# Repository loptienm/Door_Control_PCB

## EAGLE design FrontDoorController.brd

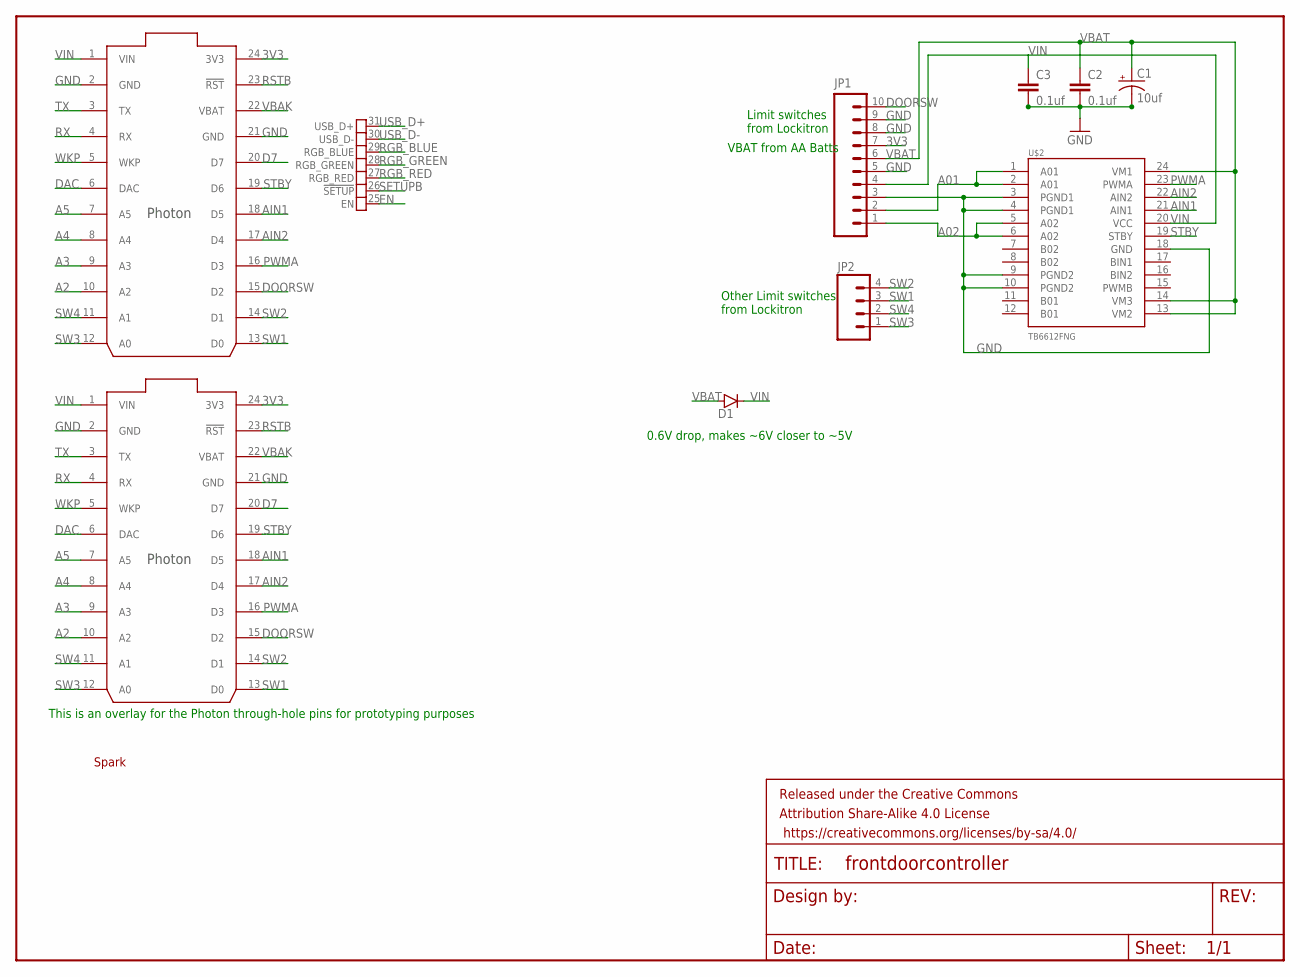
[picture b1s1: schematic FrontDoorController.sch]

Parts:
C1: 10uf; EIA3528
C2, C3: 0.1uf; 0402-CAP
D1: DIODEPTH; DIODE-1N4001
FRAME1: FRAME-LETTER; CREATIVE_COMMONS
JP1: M10LOCK; 1X10_LOCK
JP2: M04LOCK; 1X04_LOCK
PHOTON: PHOTON_SMD
U$1: SPARK_LOGOLARGE; SPARK_LOGO
U$2: TB6612FNG; SSOP24
U$3: PHOTON_WITH_HEADERS; PHOTON

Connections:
3V3: JP1.7, PHOTON.24 (3V3), U$3.24 (3V3)
A01: JP1.2, U$2.1 (A01), U$2.2 (A01)
A2: PHOTON.10 (A2), U$3.10 (A2)
A02: JP1.1, U$2.5 (A02), U$2.6 (A02)
A3: PHOTON.9 (A3), U$3.9 (A3)
A4: PHOTON.8 (A4), U$3.8 (A4)
A5: PHOTON.7 (A5), U$3.7 (A5)
AIN1: PHOTON.18 (D5), U$2.21 (AIN1), U$3.18 (D5)
AIN2: PHOTON.17 (D4), U$2.22 (AIN2), U$3.17 (D4)
D7: PHOTON.20 (D7), U$3.20 (D7)
DAC: PHOTON.6 (DAC), U$3.6 (DAC)
DOORSW: JP1.10, PHOTON.15 (D2), U$3.15 (D2)
EN: PHOTON.25 (EN)
GND: C1.C (-), C2.2, C3.2, JP1.3, JP1.5, JP1.8, JP1.9, PHOTON.2 (GND), PHOTON.21 (GND), U$2.3 (PGND1), U$2.4 (PGND1), U$2.9 (PGND2), U$2.10 (PGND2), U$2.18 (GND), U$3.2 (GND), U$3.21 (GND)
PWMA: PHOTON.16 (D3), U$2.23 (PWMA), U$3.16 (D3)
RGB_BLUE: PHOTON.29 (RGB_BLUE)
RGB_GREEN: PHOTON.28 (RGB_GREEN)
RGB_RED: PHOTON.27 (RGB_RED)
RSTB: PHOTON.23 (!RST), U$3.23 (!RST)
RX: PHOTON.4 (RX), U$3.4 (RX)
SETUPB: PHOTON.26 (!SETUP)
STBY: PHOTON.19 (D6), U$2.19 (STBY), U$3.19 (D6)
SW1: JP2.3, PHOTON.13 (D0), U$3.13 (D0)
SW2: JP2.4, PHOTON.14 (D1), U$3.14 (D1)
SW3: JP2.1, PHOTON.12 (A0), U$3.12 (A0)
SW4: JP2.2, PHOTON.11 (A1), U$3.11 (A1)
TX: PHOTON.3 (TX), U$3.3 (TX)
USB_D+: PHOTON.31 (USB_D+)
USB_D-: PHOTON.30 (USB_D-)
VBAK: PHOTON.22 (VBAT), U$3.22 (VBAT)
VBAT: C1.A (+), C2.1, D1.A, JP1.6, U$2.13 (VM2), U$2.14 (VM3), U$2.24 (VM1)
VIN: C3.1, D1.C, JP1.4, PHOTON.1 (VIN), U$2.20 (VCC), U$3.1 (VIN)
WKP: PHOTON.5 (WKP), U$3.5 (WKP)

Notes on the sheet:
VBAT from AA Batts
0.6V drop, makes ~6V closer to ~5V
This is an overlay for the Photon through-hole pins for prototyping purposes
Limit switches from Lockitron
Other Limit switches from Lockitron

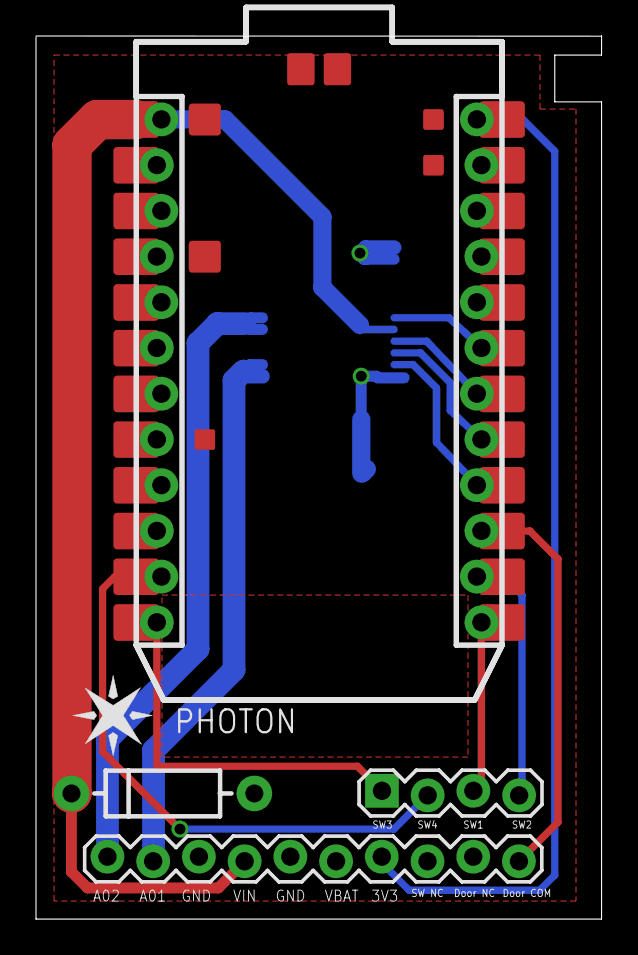
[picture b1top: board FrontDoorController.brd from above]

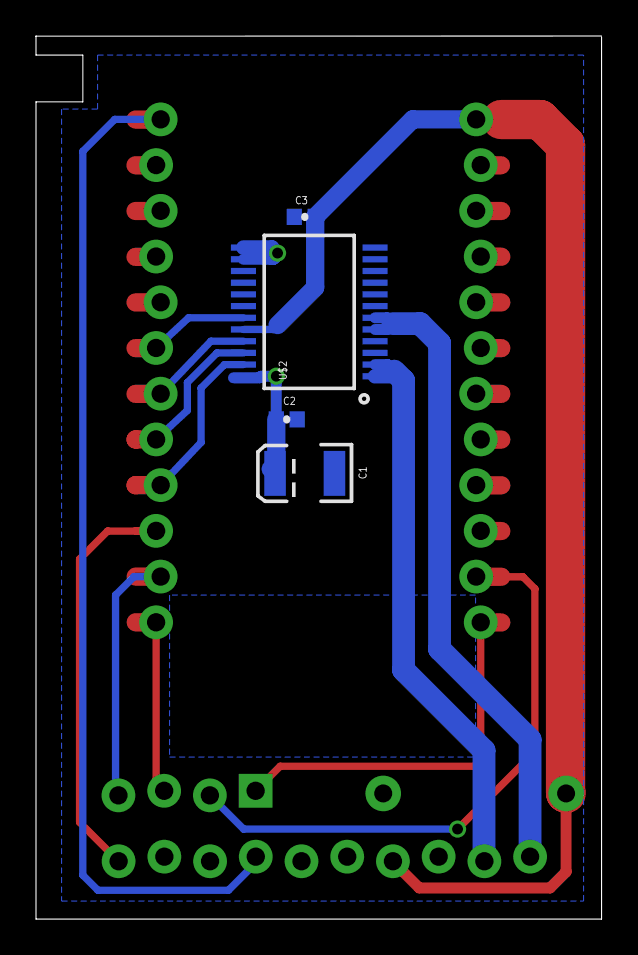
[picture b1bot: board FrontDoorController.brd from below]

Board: 2 copper layers, 31.4 x 49.1 mm, 11 parts (4 on the bottom side), 26 nets.

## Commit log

2015-07-10 :neckbeard: Added .gitattributes & .gitignore files
2015-07-10 Door_Control_PCB: Add initial Git objects
    This commit is the initial commit of the objects necessary for Git.
2015-07-10 Door_Control_PCB: Add initial Eagle schematic and board
    Add the initial Eagle schematic and board files. These are currently
    empty.
2015-07-10 Door_Control_PCB: Move the directory structure around
    Move the directory structure around to make it match the other projects
    I have going on.
2015-07-10 Door_Control_PCB: Add Photon and define board
    Add the Photon to the schematic and board and define the board outline
    including the holder tab that gets inserted into the mechanical assembly
    to hold the board in place.
2015-07-11 Door_Control_PCB: Add motor driver and connect
    Add the TB6612FNG motor driver and connect it to the Photon. This will
    take power from 4 AA batteries in the Lockitron and drive the Lockitron
    motor. The Photon will control direction and speed for the motor.
    Since there is only 1 motor on the Lockitron, only 1 of the input/output
    pairs on the driver needs to be connected.
2015-07-11 Door_Control_PCB: Add headers and diode
    Exchange the screw terminals for 0.1" breakaway header holes. There is
    no room for the screw terminals in the Lockitron so wires will need to
    be soldered directly to the board. Some space can be saved by using
    0.1" spacing header holes instead of the bigger pitch screw terminals.
    Also do a few other minor cleanup tasks like change the size of the wire
    input labels. Also add a 1N4001 diode between VM from AA's and VIN on
2015-07-11 Door_Control_PCB: Add Photon through holes
    Add in an additional part for the Photon through-hole connections. This
    can be used to attach the Photon to the board without soldering it down.
    Also reconnect the wires to the new Photon holes and clean up the
    schematic a bit.
2015-07-11 Door_Control_PCB: Shrink the board a bit to save money
    The board did not need to be nearly as big as it was and shrinking it a
    bit can save some money in maunfacturing.
2015-07-11 Door_Control_PCB: Add more header pins
    Add more header pins to be able to measure all voltages, and connect to
    the limit switches on the Lockitron to log the deadbolt position. Also
    reroute the motor drive wires to not go through the Photon through hole
    pins and make the wires larger to drive more current.
2015-07-16 Door_Control_PCB: Add reed switch connection
    Add a connection point for a reed switch to be used to sense if the door
    is open or closed. Also add a pull down resistor to ensure good
    readings and label the pins on the header.
2015-07-16 Door_Control_PCB: Change layer of labels
    Change the layer of the header labels because they didn't show up on Osh
    Park.
2015-07-16 Door_Control_PCB: Make the cutout a bit bigger
    Make the cutout and tab for the slot that holds onto the Lockitron
    mechanical assembly a bit bigger so that the fab will (hopefully) make
    it. The pictures from Sparkfun show this tab as being about 1/20th of
    an inch or about 0.05 inches (about 50 mils).
2015-07-16 Door_Control_PCB: Change layer of measurements
    Change the layer that the measurements appeared on because they are now
    showing up on Osh Park.
2015-07-16 Door_Control_PCB: Add Particle Logo
    Add the Particle (Spark) logo to the board to make it cooler looking and
    more official (not at all official).
2015-07-16 Door_Control_PCB: Update to the Eagle EPF file
    I don't really know what is in this change but a few things changed...
2015-07-19 Door_Control_PCB: Add locking Photon and reroute
    Add the locking Photon from Mike's Library so that I can try out the
    connections before soldering. Also reroute some things and make a few
    traces bigger and move some of the header pins around.
2015-07-19 Door_Control_PCB: Add SW3 and SW4 from Lockitron
    The Lockitron has 4 limit switches instead of 2 like I originally
    thought. They also need a common place to wire their NC connections to
    and with this many switches it seemed best to give them their own header
    row, causing some other components to have to move and some other pins
    to need moving as well. Things all seem to flow well now and there
    should be plenty of power to all of the components.
2015-07-19 Door_Control_PCB: Widen Motor A01/2 traces
    These were probably wide enough but I thought that giving them as much
    surface area as possible to transmit high current to the motor is a good
    thing so I widened the traces by a bit. This also made the connections
    to the IC pads much prettier.

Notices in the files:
parts and their libraries:
SparkFun-Aesthetics: Licensing: Creative Commons ShareAlike 4.0 International - https://creativecommons.org/licenses/by-sa/4.0
SparkFun-Aesthetics: Released under the Creative Commons Attribution Share-Alike 4.0 License
SparkFun-Aesthetics: https://creativecommons.org/licenses/by-sa/4.0
